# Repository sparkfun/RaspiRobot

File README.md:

RaspiRobot Board
================

[  
*RaspiRobot Board (KIT-11561)*](https://www.sparkfun.com/products/11561)

The RaspiRobot Board is an expansion board for the Raspberry Pi that turns it into a robot controller. This repository contains EAGLE hardware files for the RaspiRobot Board.

Documentation for the RaspiRobot board can be found at [http://www.raspirobot.com/](http://www.raspirobot.com/).

License Information
-------------------

The hardware is released under [Creative Commons Share-alike 3.0](http://creativecommons.org/licenses/by-sa/3.0/).

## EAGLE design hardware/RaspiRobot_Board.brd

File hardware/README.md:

RaspiRobot Board
====

These are the Eagle hardware design files for the [RaspiRobot Board](https://www.sparkfun.com/products/11561).

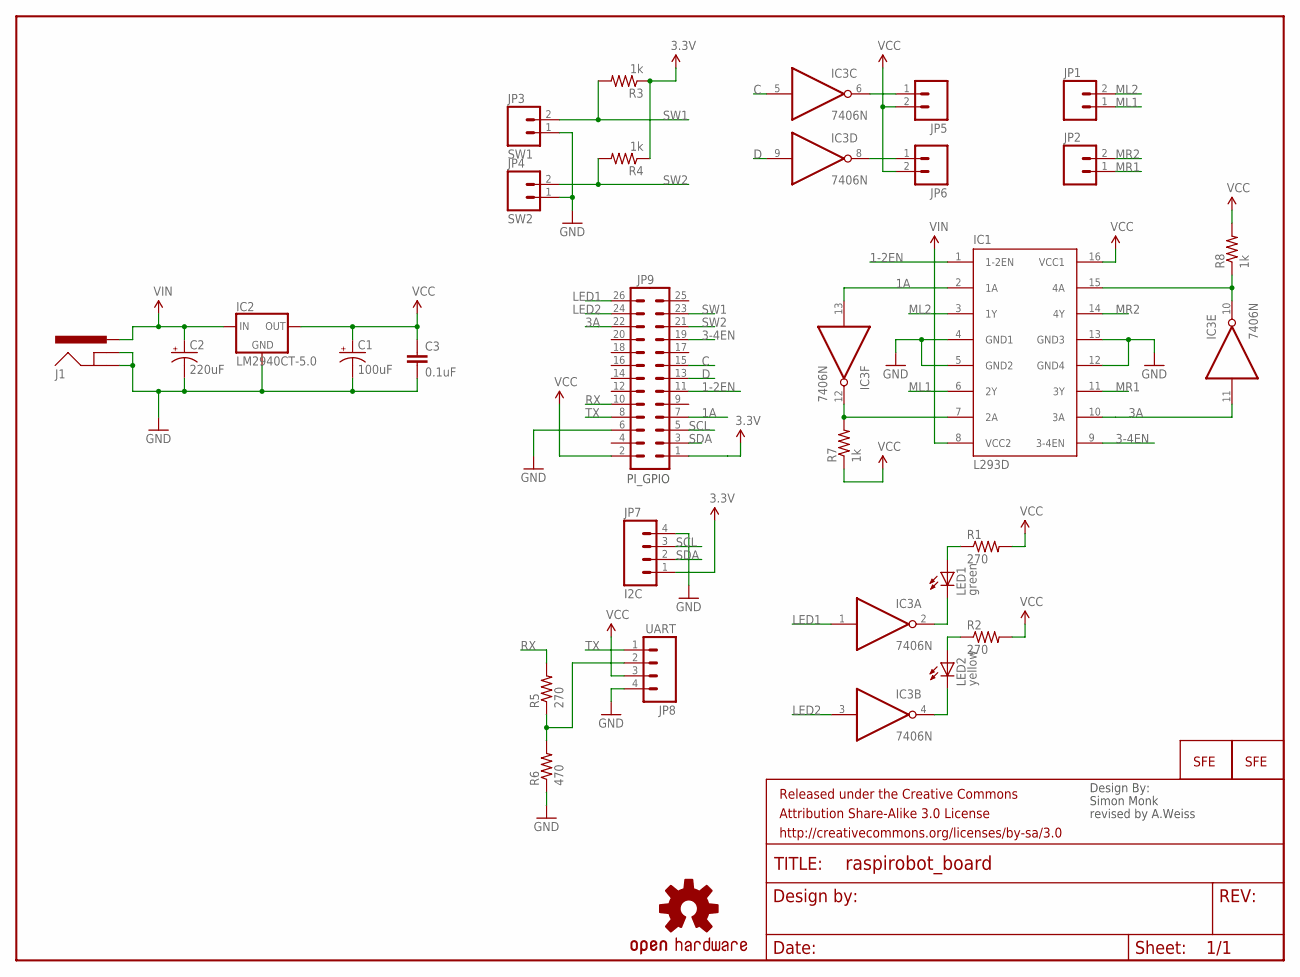
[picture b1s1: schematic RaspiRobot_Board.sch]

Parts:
C1: 100uF; CPOL-RADIAL-100UF-25V
C2: 220uF; CPOL-RADIAL-100UF-25V
C3: 0.1uF; CAP-PTH-SMALL-KIT
FRAME1: FRAME-LETTER; CREATIVE_COMMONS
IC1: L293D; DIL16
IC2: LM2940CT-5.0; TO220-IGO
IC3: 7406N; DIL14
J1: POWER_JACKPTH_LOCK; POWER_JACK_PTH_LOCK
JP1, JP2: M023.5MM_LOCK; SCREWTERMINAL-3.5MM-2_LOCK
JP3: SW1; 1X02
JP4: SW2; 1X02
JP5, JP6: M02PTH; 1X02
JP7: I2C; 1X04
JP8: UART; 1X04
JP9: M13X22X13; 2X13
JP10, JP11: LOGO-SFENEW; SFE-NEW-WEBLOGO
LED1: green; LED3MM
LED2: yellow; LED3MM
R1, R2, R5: 270; AXIAL-0.3EZ
R3, R4, R7, R8: 1k; AXIAL-0.3EZ
R6: 470; AXIAL-0.3EZ
U$4: OSHW-LOGOS; OSHW-LOGO-S

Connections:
1-2EN: IC1.1 (1-2EN), JP9.11
1A: IC1.2 (1A), IC3.13 (I), JP9.7
3-4EN: IC1.9 (3-4EN), JP9.19
3.3V: JP7.1, JP9.1, R3.P$1 (1), R4.P$1 (1)
3A: IC1.10 (3A), IC3.11 (I), JP9.22
C: IC3.5 (I), JP9.15
D: IC3.9 (I), JP9.13
GND: C1.2 (-), C2.2 (-), C3.2, IC1.4 (GND1), IC1.5 (GND2), IC1.12 (GND4), IC1.13 (GND3), IC2.GND, IC3.7 (GND), J1.GND, J1.GNDBREAK, JP3.1, JP4.1, JP7.4, JP8.4, JP9.6, R6.P$1 (1)
LED1: IC3.1 (I), JP9.26
LED2: IC3.3 (I), JP9.24
ML1: IC1.6 (2Y), JP1.1
ML2: IC1.3 (1Y), JP1.2
MR1: IC1.11 (3Y), JP2.1
MR2: IC1.14 (4Y), JP2.2
unnamed: IC1.7 (2A), IC3.12 (O), R7.P$2 (2)
unnamed: IC1.15 (4A), IC3.10 (O), R8.P$1 (1)
unnamed: LED1.A, R1.P$1 (1)
unnamed: LED2.A, R2.P$1 (1)
unnamed: IC3.2 (O), LED1.K (C)
unnamed: IC3.4 (O), LED2.K (C)
unnamed: IC3.6 (O), JP5.1
unnamed: IC3.8 (O), JP6.1
unnamed: JP8.2, R5.P$1 (1), R6.P$2 (2)
RX: JP9.10, R5.P$2 (2)
SCL: JP7.3, JP9.5
SDA: JP7.2, JP9.3
SW1: JP3.2, JP9.23, R3.P$2 (2)
SW2: JP4.2, JP9.21, R4.P$2 (2)
TX: JP8.1, JP9.8
VCC: C1.1 (+), C3.1, IC1.16 (VCC1), IC2.OUT, IC3.14 (VCC), JP5.2, JP6.2, JP8.3, JP9.2, R1.P$2 (2), R2.P$2 (2), R7.P$1 (1), R8.P$2 (2)
VIN: C2.1 (+), IC1.8 (VCC2), IC2.IN, J1.PWR

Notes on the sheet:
Simon Monk
revised by A.Weiss
PI_GPIO
Design By:

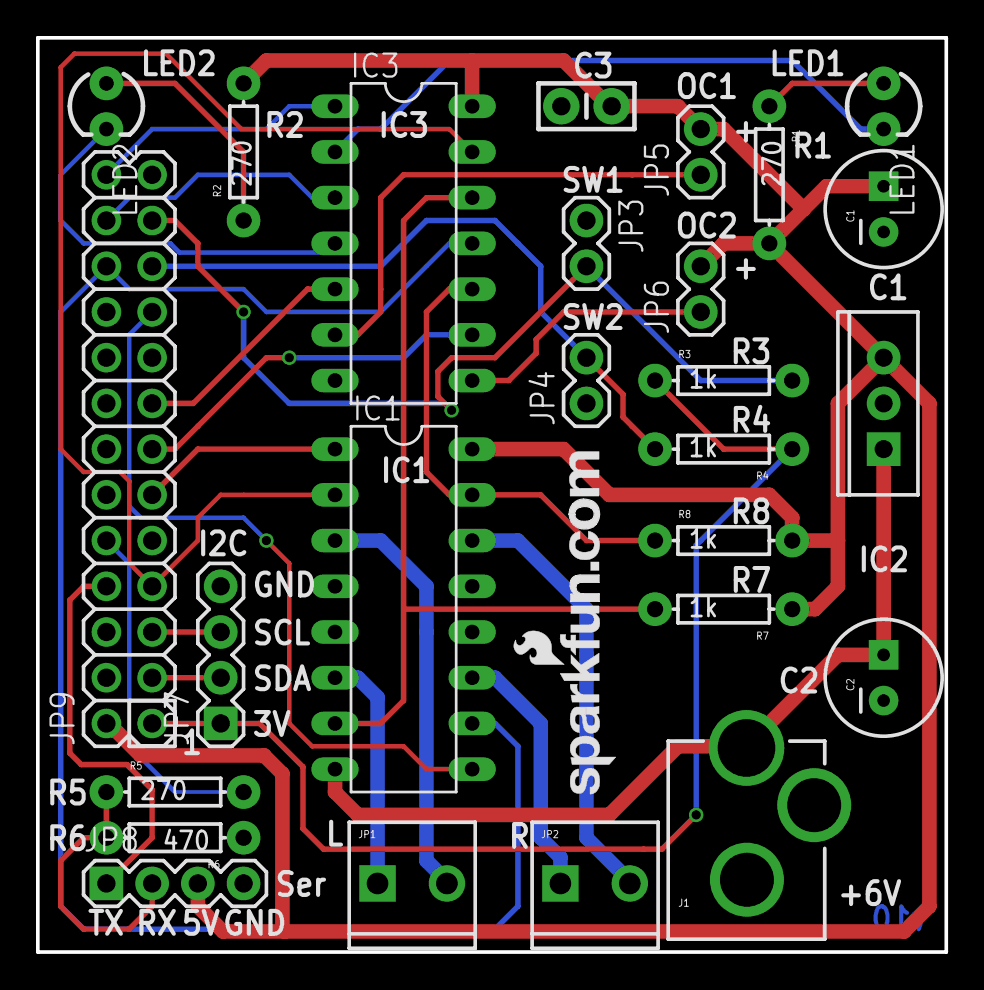
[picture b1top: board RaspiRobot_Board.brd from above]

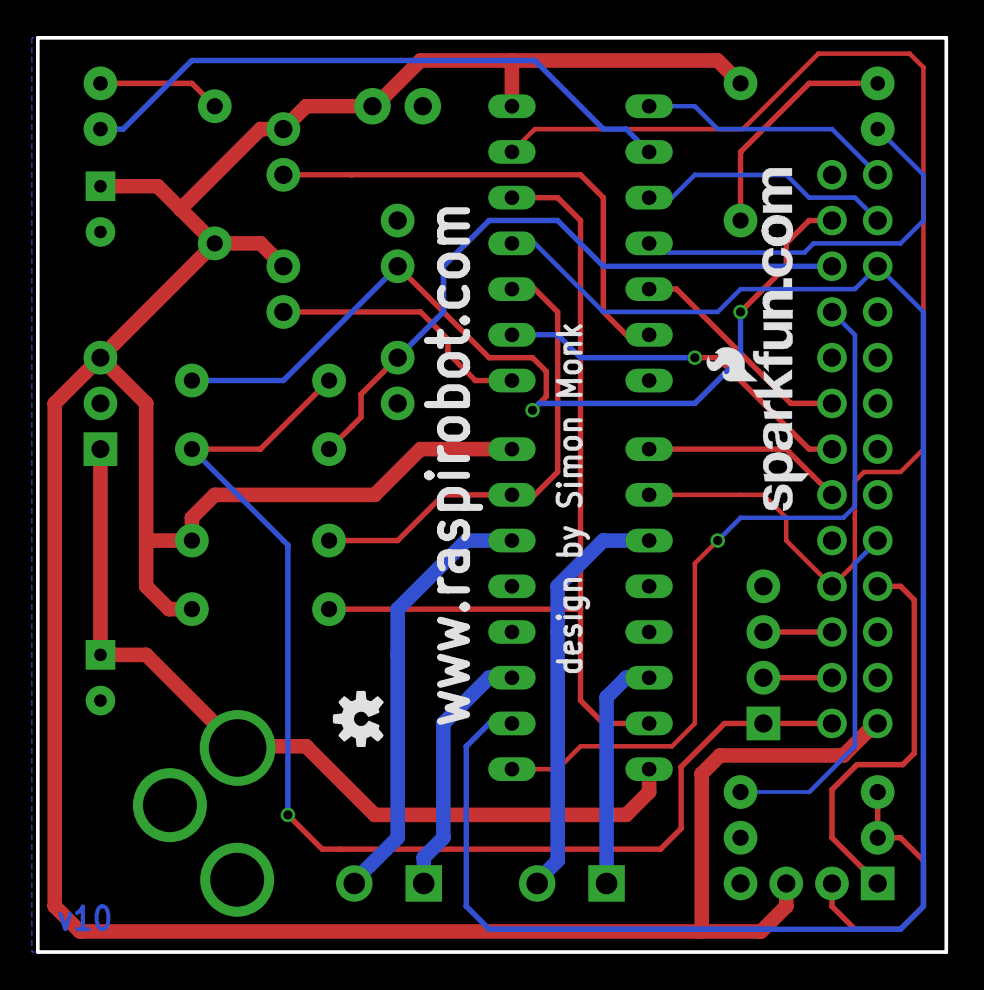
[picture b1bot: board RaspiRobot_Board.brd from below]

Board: 2 copper layers, 50.5 x 50.8 mm, 30 parts (2 on the bottom side), 31 nets.

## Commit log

2013-02-13 v10 production hardware
2013-03-07 fleshing out readme, adding image/links/etc.

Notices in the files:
parts and their libraries:
SparkFun-Aesthetics: Licensing: CC v3.0 Share-Alike You are welcome to use this library for commercial purposes.
SparkFun-Aesthetics: Released under the Creative Commons Attribution Share-Alike 3.0 License
SparkFun-Aesthetics: Released under the Creative Commons
